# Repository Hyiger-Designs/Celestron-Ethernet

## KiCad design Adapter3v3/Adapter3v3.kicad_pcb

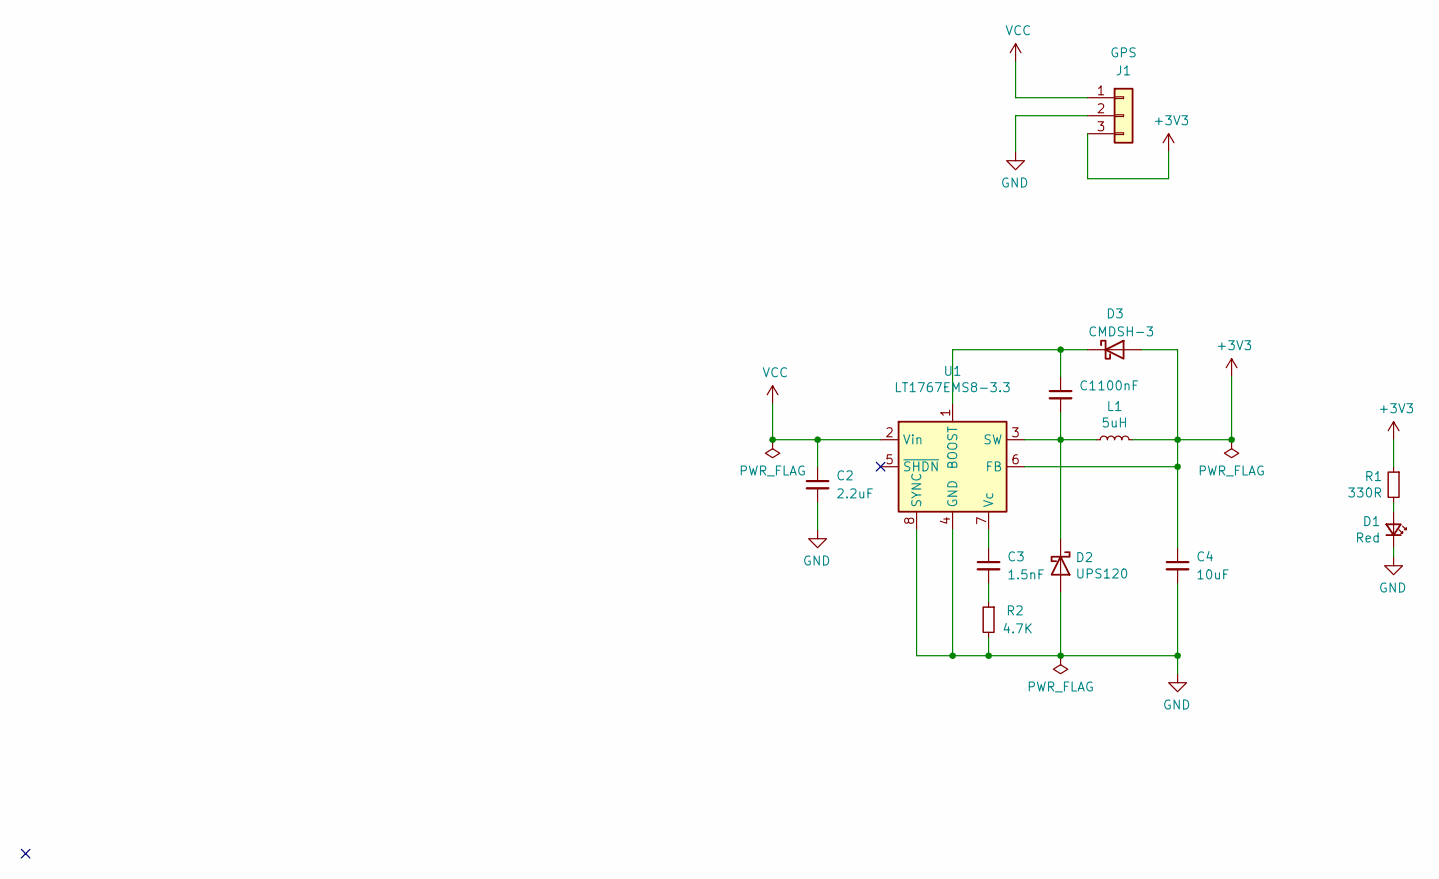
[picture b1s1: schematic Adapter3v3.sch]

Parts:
C1: 100nF; C_0603_1608Metric
C2: 2.2uF; C_0603_1608Metric
C3: 1.5nF; C_0603_1608Metric
C4: 10uF; C_0603_1608Metric
D1: Red; LED_0603_1608Metric
D2: UPS120; D_Powermite_KA
D3: CMDSH-3; D_SOD-323
J1: GPS; PinHeader_1x03_P2.54mm_Horizontal_Flipped
L1: 5uH; L_Wuerth_WE-PDF; MPN MSS6132-473MLC
R1: 330R; R_0603_1608Metric
R2: 4.7K; R_0603_1608Metric
U1: LT1767EMS8-3.3; MSOP-8_3x3mm_P0.65mm

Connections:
+3V3: C4.1, D3.2 (A), J1.3, L1.2, R1.1, U1.6 (FB)
GND: C2.2, C4.2, D1.1 (K), D2.2 (A), J1.2, R2.2, U1.4 (GND), U1.8 (SYNC)
unnamed: C1.1, D3.1 (K), U1.1 (BOOST)
unnamed: C1.2, D2.1 (K), L1.1, U1.3 (SW)
unnamed: C3.1, U1.7 (Vc)
unnamed: C3.2, R2.1
unnamed: D1.2 (A), R1.2
VCC: C2.1, J1.1, U1.2 (Vin)

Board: 2 copper layers, 12 parts (0 on the bottom side), 8 nets, no tracks yet.

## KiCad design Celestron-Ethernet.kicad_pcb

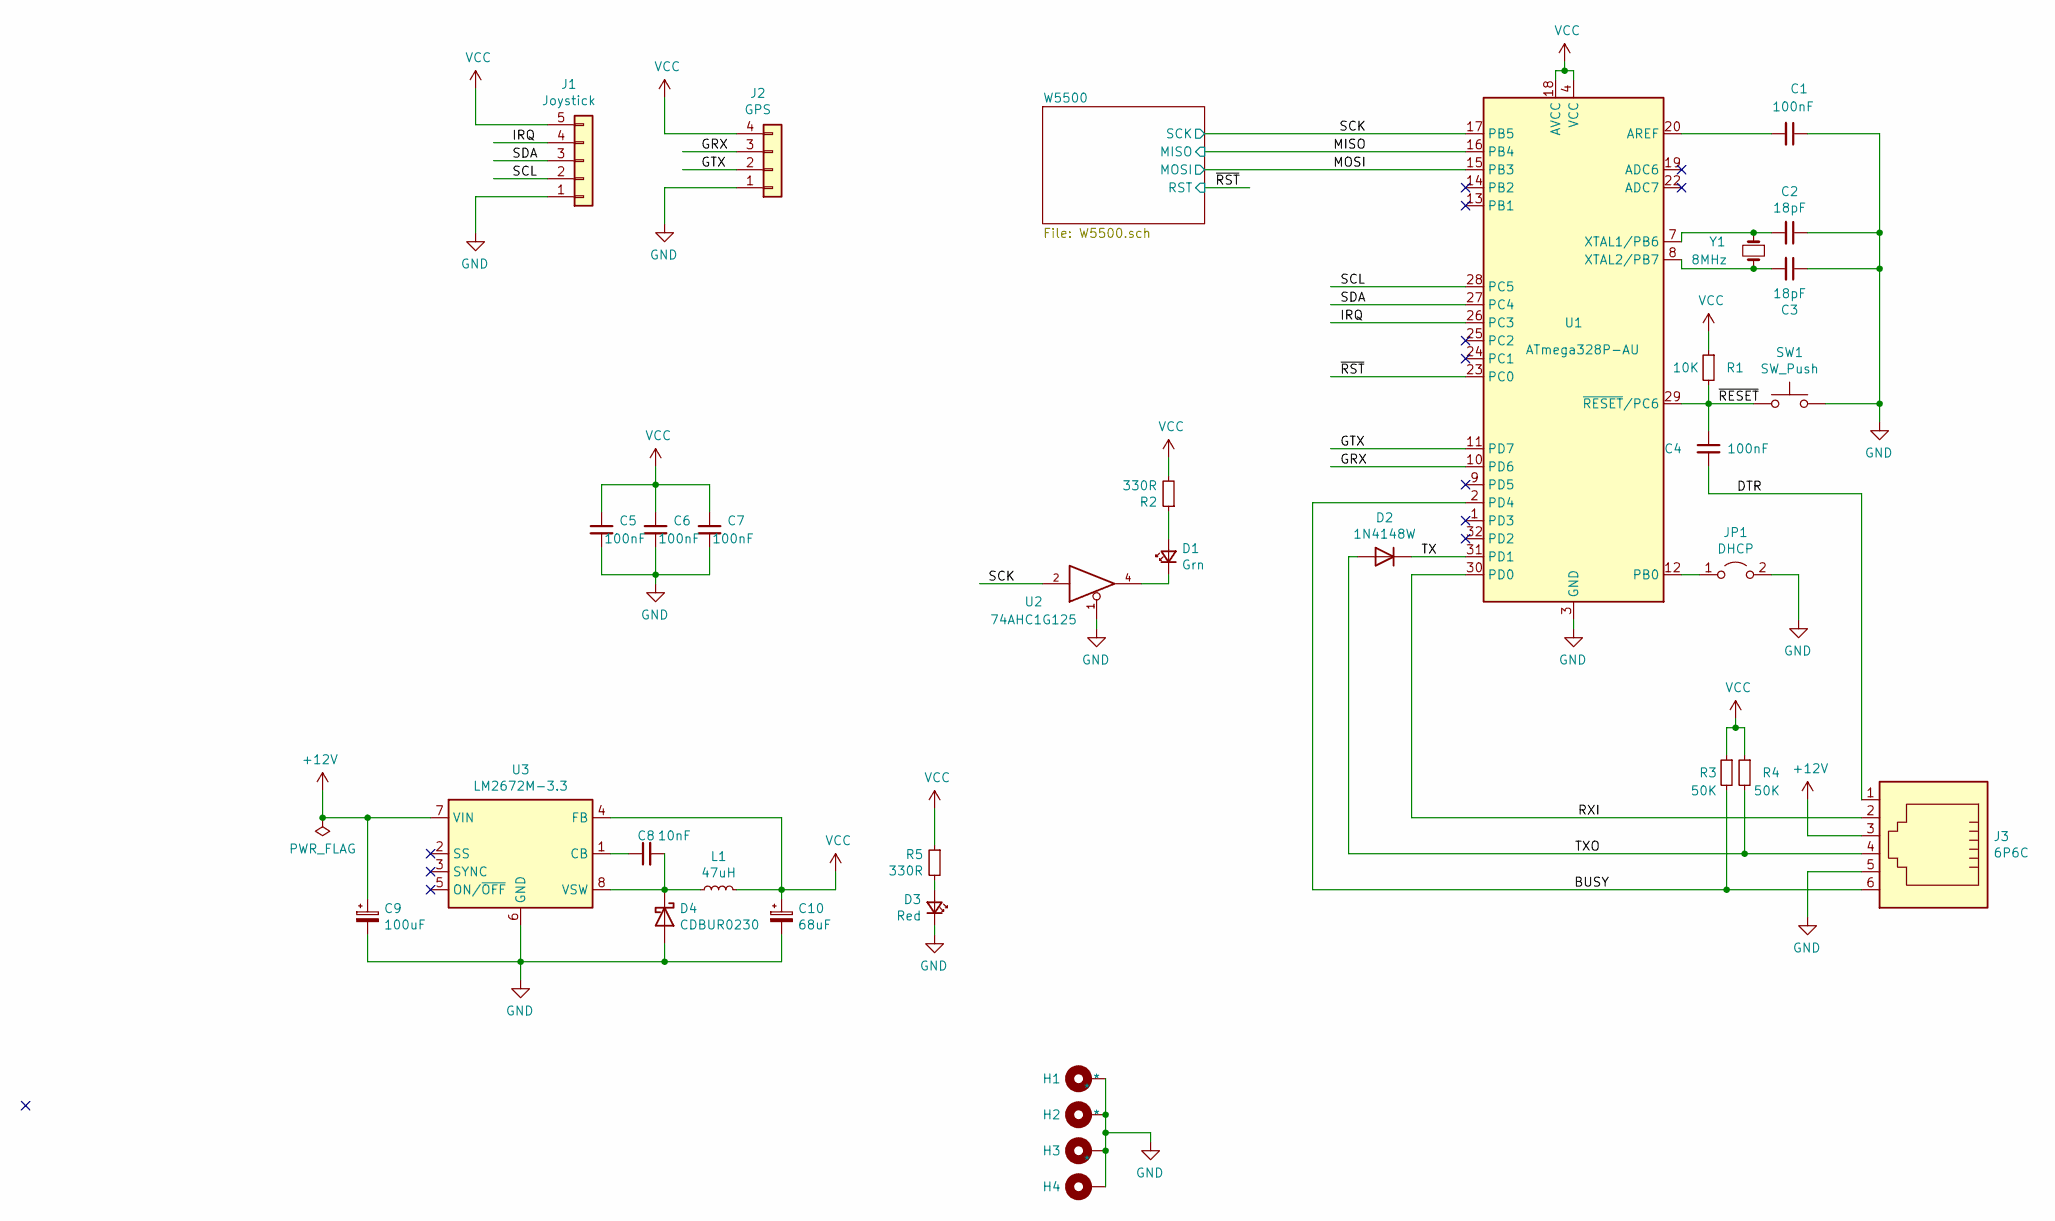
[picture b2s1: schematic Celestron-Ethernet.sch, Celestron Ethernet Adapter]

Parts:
C1, C4, C5, C6, C7: 100nF; C_0603_1608Metric
C2, C3: 18pF; C_0603_1608Metric
C8: 10nF; C_0603_1608Metric
C9: 100uF; CP_EIA-2012-12_Kemet-R
C10: 68uF; CP_EIA-2012-12_Kemet-R
D1: Grn; LED_0603_1608Metric
D2: 1N4148W; D_SOD-323F
D3: Red; LED_0603_1608Metric
D4: CDBUR0230; D_0603_1608Metric
H1, H2, H3, H4: *; MountingHole_2.2mm_M2_Pad_Via
J1: Joystick; JST_SH_BM05B-SRSS-TB_1x05-1MP_P1.00mm_Vertical
J2: GPS; JST_SH_BM04B-SRSS-TB_1x04-1MP_P1.00mm_Vertical
J3: 6P6C; RJ12_Amphenol_54601; MPN 54601-906001WPLF
JP1: DHCP; PinHeader_1x02_P2.54mm_Vertical
L1: 47uH; L_Coilcraft_LPS5030; MPN MSS6132-473MLC
R1: 10K; R_0603_1608Metric
R2, R5: 330R; R_0603_1608Metric
R3, R4: 50K; R_0603_1608Metric
SW1: SW_Push; SW_SPST_FSMSM
U1: ATmega328P-AU; TQFP-32_7x7mm_P0.8mm; MPN ATMEGA328-AU
U2: 74AHC1G125; SOT-23-5
U3: LM2672M-3.3; SOIC-8_3.9x4.9mm_P1.27mm
Y1: 8MHz; Crystal_SMD_0603-2Pin_6.0x3.5mm; MPN 406C35D08M00000

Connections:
+12V: C9.1, J3.3, U3.7 (VIN)
/BUSY: J3.6, R3.2, U1.2 (PD4)
/DTR: C4.2, J3.1
/GRX: J2.3, U1.10 (PD6)
/GTX: J2.2, U1.11 (PD7)
/IRQ: J1.4, U1.26 (PC3)
/MISO: U1.16 (PB4); also elsewhere on the board
/MOSI: U1.15 (PB3); also elsewhere on the board
/RXI: J3.2, U1.30 (PD0)
/SCK: U1.17 (PB5), U2.2; also elsewhere on the board
/SCL: J1.2, U1.28 (PC5)
/SDA: J1.3, U1.27 (PC4)
/TX: D2.1 (K), U1.31 (PD1)
/TXO: D2.2 (A), J3.4, R4.2
/~RESET: C4.1, R1.2, SW1.2, U1.29 (~RESET~/PC6)
/~RST: U1.23 (PC0); also elsewhere on the board
GND: C1.1, C2.1, C3.1, C5.2, C6.2, C7.2, C9.2, C10.2, D3.1 (K), D4.2 (A), H1.1, H2.1, H3.1, H4.1, J1.1, J2.1, J3.5, JP1.2 (B), SW1.1, U1.3 (GND), U1.5 (GND), U1.21 (GND), U2.1, U2.3 (GND), U3.6 (GND); also elsewhere on the board
unnamed: C1.2, U1.20 (AREF)
unnamed: C2.2, U1.7 (XTAL1/PB6), Y1.1
unnamed: C3.2, U1.8 (XTAL2/PB7), Y1.2
unnamed: C8.1, U3.1 (CB)
unnamed: C8.2, D4.1 (K), L1.1, U3.8 (VSW)
unnamed: D1.1 (K), U2.4
unnamed: D1.2 (A), R2.1
unnamed: D3.2 (A), R5.2
unnamed: JP1.1 (A), U1.12 (PB0)
VCC: C5.1, C6.1, C7.1, C10.1, J1.5, J2.4, L1.2, R1.1, R2.2, R3.1, R4.1, R5.1, U1.4 (VCC), U1.6 (VCC), U1.18 (AVCC), U2.5 (VCC), U3.4 (FB); also elsewhere on the board

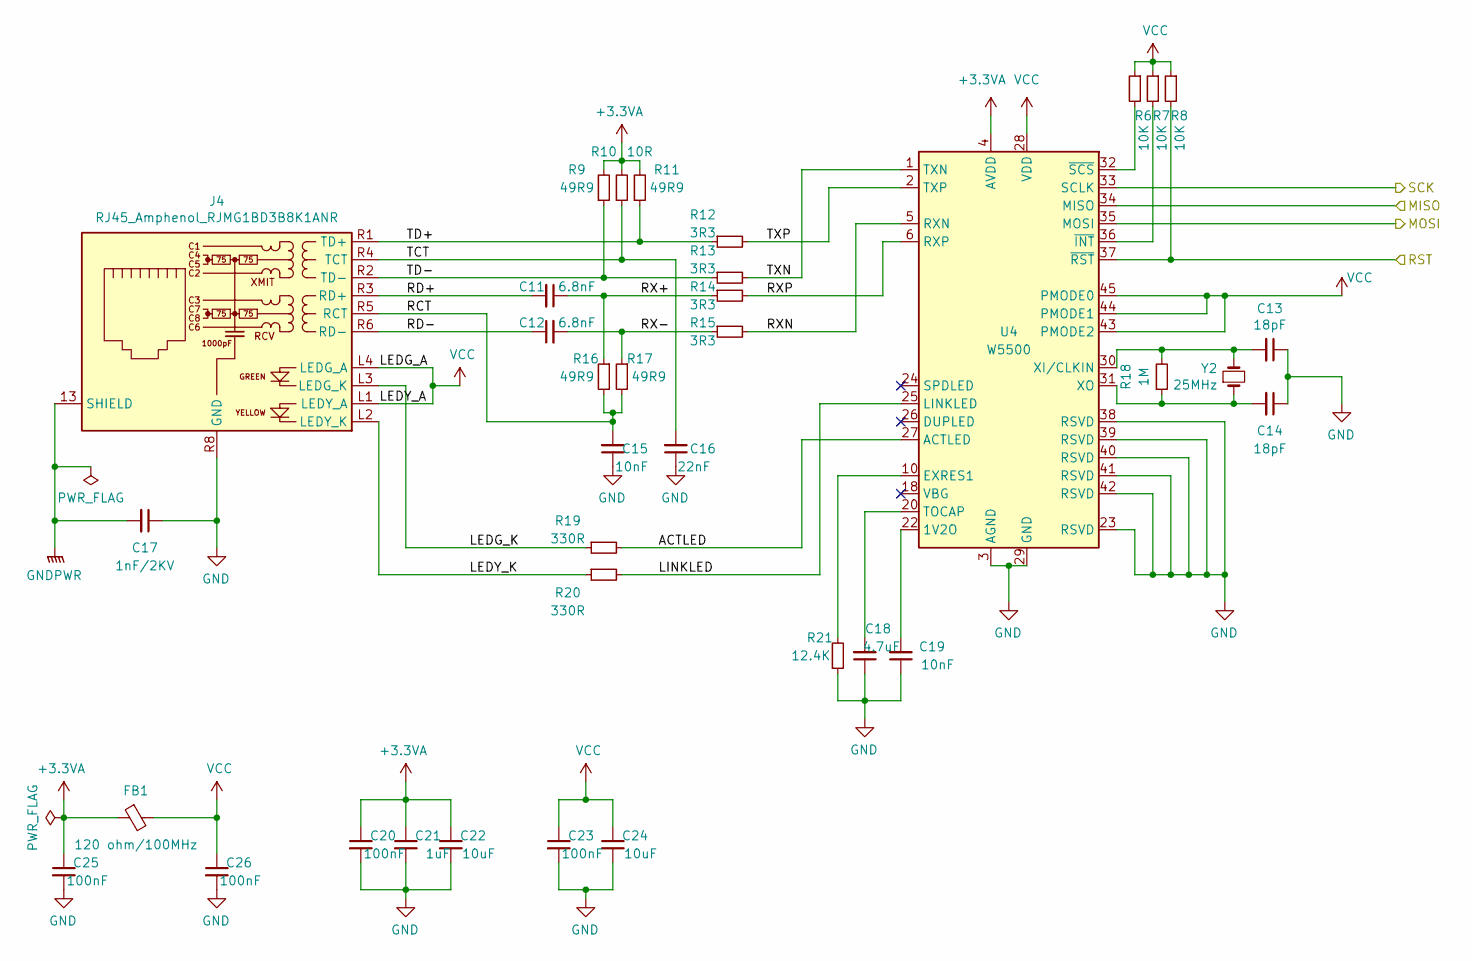
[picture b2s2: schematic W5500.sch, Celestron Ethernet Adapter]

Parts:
C11, C12: 6.8nF; C_0603_1608Metric; MPN C0603C682J4HACTU
C13, C14: 18pF; C_0603_1608Metric
C15, C19: 10nF; C_0603_1608Metric
C16: 22nF; C_0603_1608Metric
C17: 1nF/2KV; C_1206_3216Metric; MPN C1206C102KGRACTU
C18: 4.7uF; C_0603_1608Metric; MPN GRM188R61C475KE11D
C20, C23, C25, C26: 100nF; C_0603_1608Metric
C21: 1uF; C_0603_1608Metric
C22, C24: 10uF; C_0603_1608Metric
FB1: 120 ohm/100MHz; L_0603_1608Metric; MPN FBMH1608HL121-T
J4: RJ45_Amphenol_RJMG1BD3B8K1ANR; MPN RJMG1BD3B8K1ANR
R6, R7, R8: 10K; R_0603_1608Metric
R9, R11, R16, R17: 49R9; R_0603_1608Metric
R10: 10R; R_0603_1608Metric
R12, R13, R14, R15: 3R3; R_0603_1608Metric
R18: 1M; R_0603_1608Metric
R19, R20: 330R; R_0603_1608Metric
R21: 12.4K; R_0603_1608Metric
U4: W5500; LQFP-48_7x7mm_P0.5mm; MPN W5500
Y2: 25MHz; Crystal_SMD_0603-2Pin_6.0x3.5mm; MPN 406C35D25M00000

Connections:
+3.3VA: C20.1, C21.1, C22.1, C25.1, FB1.1, R9.2, R10.2, R11.2, U4.4 (AVDD), U4.8 (AVDD), U4.11 (AVDD), U4.15 (AVDD), U4.17 (AVDD), U4.21 (AVDD)
/MISO: U4.34 (MISO); also elsewhere on the board
/MOSI: U4.35 (MOSI); also elsewhere on the board
/SCK: U4.33 (SCLK); also elsewhere on the board
/W5500/ACTLED: R19.2, U4.27 (ACTLED)
/W5500/LEDG_K: J4.L3 (LEDG_K), R19.1
/W5500/LEDY_K: J4.L2 (LEDY_K), R20.1
/W5500/LINKLED: R20.2, U4.25 (LINKLED)
/W5500/RCT: C15.2, J4.R5 (RCT), R16.2, R17.2
/W5500/RD+: C11.2, J4.R3 (RD+)
/W5500/RD-: C12.1, J4.R6 (RD-)
/W5500/RX+: C11.1, R14.1, R16.1
/W5500/RX-: C12.2, R15.1, R17.1
/W5500/RXN: R15.2, U4.5 (RXN)
/W5500/RXP: R14.2, U4.6 (RXP)
/W5500/TCT: C16.2, J4.R4 (TCT), R10.1
/W5500/TD+: J4.R1 (TD+), R11.1, R12.1
/W5500/TD-: J4.R2 (TD-), R9.1, R13.1
/W5500/TXN: R13.2, U4.1 (TXN)
/W5500/TXP: R12.2, U4.2 (TXP)
/~RST: R8.2, U4.37 (~RST); also elsewhere on the board
GND: C13.1, C14.1, C15.1, C16.1, C17.1, C18.1, C19.1, C20.2, C21.2, C22.2, C23.2, C24.2, C25.2, C26.2, J4.R8 (GND), R21.1, U4.3 (AGND), U4.9 (AGND), U4.14 (AGND), U4.16 (AGND), U4.19 (AGND), U4.23 (RSVD), U4.29 (GND), U4.38 (RSVD), U4.39 (RSVD), U4.40 (RSVD), U4.41 (RSVD), U4.42 (RSVD), U4.48 (AGND); also elsewhere on the board
GNDPWR: C17.2, J4.13 (SHIELD)
unnamed: C13.2, R18.2, U4.30 (XI/CLKIN), Y2.2
unnamed: C14.2, R18.1, U4.31 (XO), Y2.1
unnamed: C18.2, U4.20 (TOCAP)
unnamed: C19.2, U4.22 (1V2O)
unnamed: R6.2, U4.32 (~SCS)
unnamed: R7.2, U4.36 (~INT)
unnamed: R21.2, U4.10 (EXRES1)
VCC: C23.1, C24.1, C26.1, FB1.2, J4.L1 (LEDY_A), J4.L4 (LEDG_A), R6.1, R7.1, R8.1, U4.28 (VDD), U4.43 (PMODE2), U4.44 (PMODE1), U4.45 (PMODE0); also elsewhere on the board

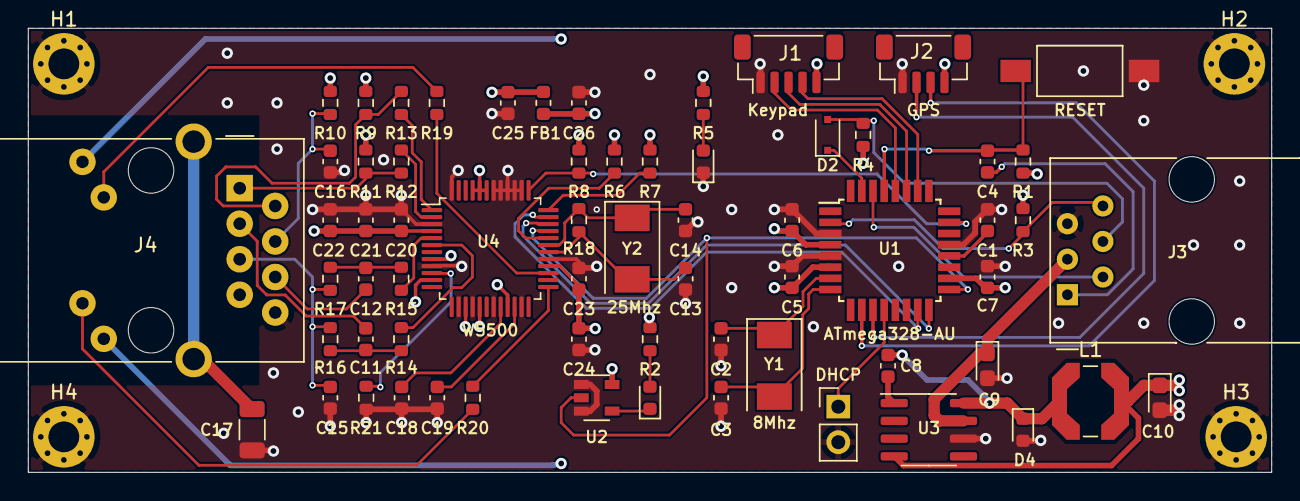
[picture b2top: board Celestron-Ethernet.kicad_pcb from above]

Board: 4 copper layers, 88.9 x 31.8 mm, 69 parts (0 on the bottom side), 52 nets.

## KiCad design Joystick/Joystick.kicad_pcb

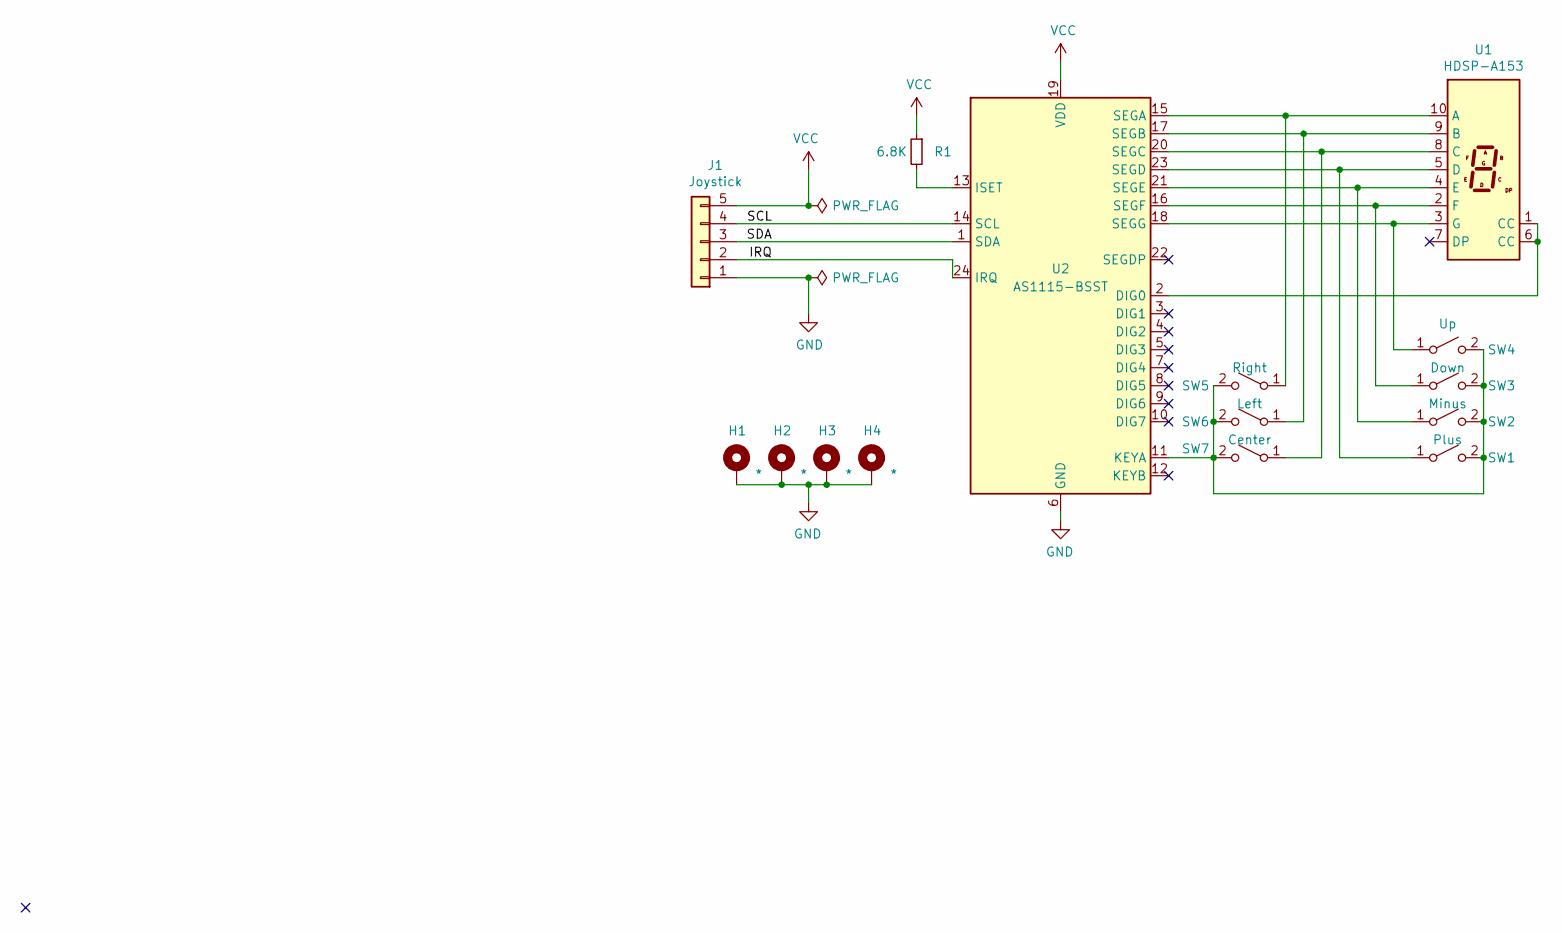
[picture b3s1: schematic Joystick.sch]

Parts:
H1, H2, H3, H4: *; MountingHole_3.2mm_M3_Pad_Via
J1: Joystick; JST_GH_SM05B-GHS-TB_1x05-1MP_P1.25mm_Horizontal
R1: 6.8K; R_0603_1608Metric
SW1: Plus; SW_Cherry_MX_1.00u_PCB
SW2: Minus; SW_Cherry_MX_1.00u_PCB
SW3: Down; SW_Cherry_MX_1.00u_PCB
SW4: Up; SW_Cherry_MX_1.00u_PCB
SW5: Right; SW_Cherry_MX_1.00u_PCB
SW6: Left; SW_Cherry_MX_1.00u_PCB
SW7: Center; SW_Cherry_MX_1.00u_PCB
U1: HDSP-A153; HDSP-A151
U2: AS1115-BSST; QSOP-24_3.9x8.7mm_P0.635mm

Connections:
/IRQ: J1.2, U2.24 (IRQ)
/SCL: J1.4, U2.14 (SCL)
/SDA: J1.3, U2.1 (SDA)
GND: H1.1, H2.1, H3.1, H4.1, J1.1, U2.6 (GND)
unnamed: R1.2, U2.13 (ISET)
unnamed: SW1.1 (A), U1.5 (D), U2.23 (SEGD)
unnamed: SW1.2 (B), SW2.2 (B), SW3.2 (B), SW4.2 (B), SW5.2 (B), SW6.2 (B), SW7.2 (B), U2.11 (KEYA)
unnamed: SW2.1 (A), U1.4 (E), U2.21 (SEGE)
unnamed: SW3.1 (A), U1.2 (F), U2.16 (SEGF)
unnamed: SW4.1 (A), U1.3 (G), U2.18 (SEGG)
unnamed: SW5.1 (A), U1.10 (A), U2.15 (SEGA)
unnamed: SW6.1 (A), U1.9 (B), U2.17 (SEGB)
unnamed: SW7.1 (A), U1.8 (C), U2.20 (SEGC)
unnamed: U1.1 (CC), U1.6 (CC), U2.2 (DIG0)
VCC: J1.5, R1.1, U2.19 (VDD)

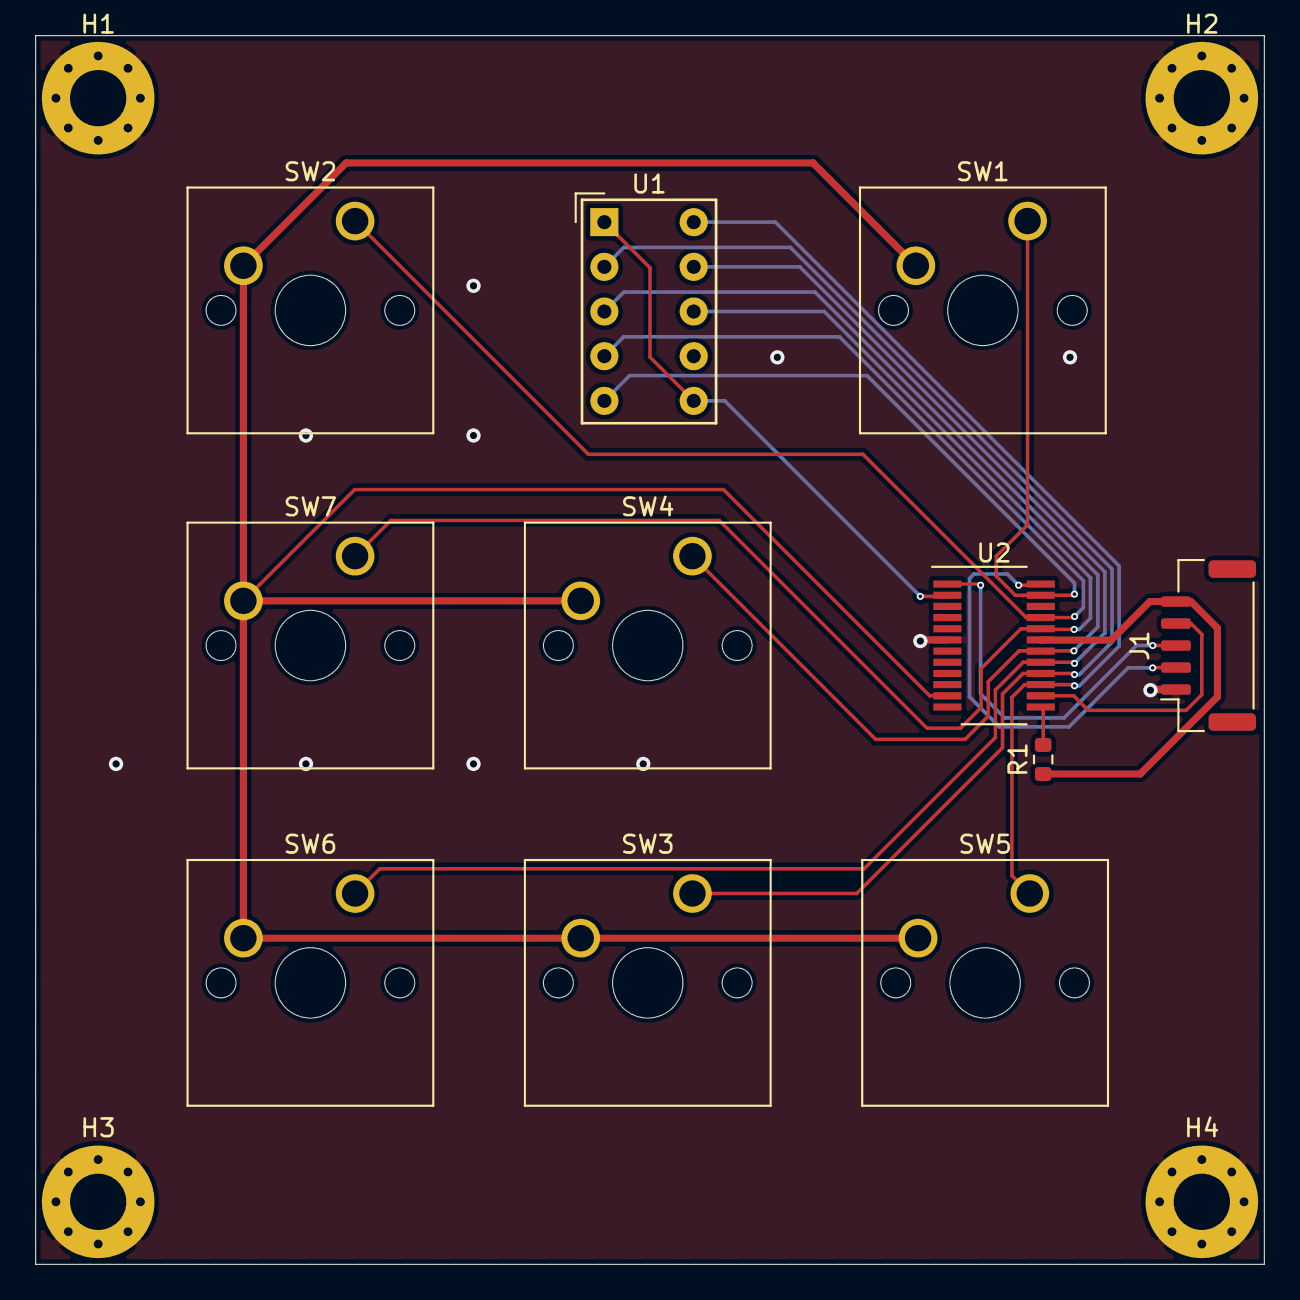
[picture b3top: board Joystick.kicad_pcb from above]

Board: 2 copper layers, 69.8 x 69.8 mm, 15 parts (0 on the bottom side), 15 nets.

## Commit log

2021-11-08 Initial version
2021-11-08 Initial routing
2021-11-08 bypass caps
2021-11-08 corrected w5500 schematic, added mounting holes
2021-11-09 traces complete
2021-11-10 silkscreen
2021-11-11 schematic fixes, moved copper planes
2021-11-11 Added aux port pullups
2021-11-12 3v3 version
2021-11-12 Added GPS connectors
2021-11-13 Separated W5500 schematic, added joystick interface
2021-11-15 joystick interface
2021-11-15 W5500 fixes
2021-11-16 cleanup
2021-11-17 grid spacing
2021-11-17 Layout fixed
2021-11-18 finished routing
2021-11-19 final version
2021-11-20 sent to fab
2021-11-20 Version 1.0
2021-11-20 adapter
2021-11-22 programming adapter
2021-11-25 keypad
2021-11-26 buck converter
